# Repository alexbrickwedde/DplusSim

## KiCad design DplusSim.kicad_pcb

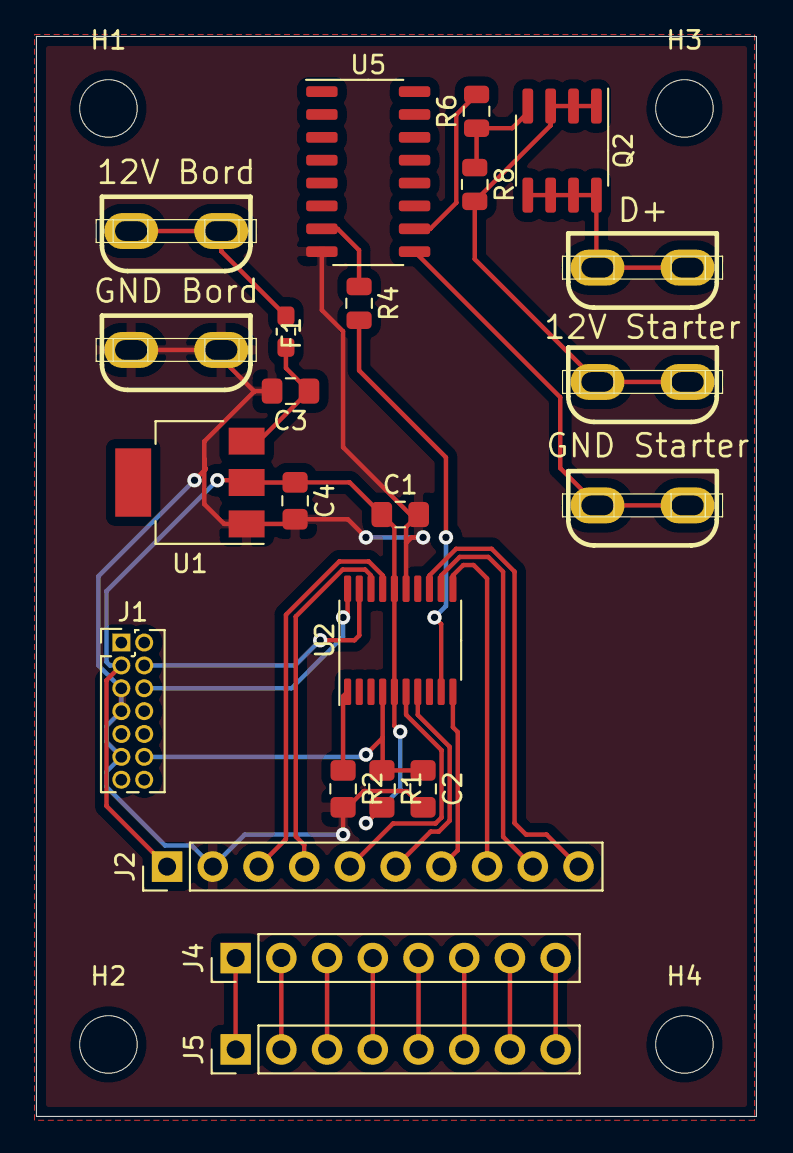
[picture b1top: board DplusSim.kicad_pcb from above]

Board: 2 copper layers, 40.0 x 60.0 mm, 27 parts (0 on the bottom side), 31 nets.

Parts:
C1: 100n; C_0805_2012Metric_Pad1.15x1.40mm_HandSolder
C2, C3, C4: C; C_0805_2012Metric_Pad1.15x1.40mm_HandSolder
F1: Polyfuse; R_0603_1608Metric_Pad1.05x0.95mm_HandSolder
H1, H2, H3, H4: MountingHole; MountingHole_3.2mm_M3_DIN965
J1: Conn_02x07_Odd_Even; PinHeader_2x07_P1.27mm_Vertical
J2: Conn_01x10; PinHeader_1x10_P2.54mm_Vertical
J3: GND Starter; FASTON-6_3mm
J4, J5: Conn_01x08; PinHeader_1x08_P2.54mm_Vertical
J6: 12V Starter; FASTON-6_3mm
J7: 12V Bord; FASTON-6_3mm
J8: GND Bord; FASTON-6_3mm
J11: D+; FASTON-6_3mm
Q2: IRF7404; SOIC-8_3.9x4.9mm_P1.27mm
R1, R2: R; R_0805_2012Metric_Pad1.15x1.40mm_HandSolder
R4, R6, R8: R; R_0805_2012Metric
U1: LT1117-3.3; SOT-223
U2: STM32L031F4Px; TSSOP-20_4.4x6.5mm_P0.65mm
U5: LTV-847; SO-16_3.9x9.9mm_P1.27mm

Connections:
+3V3: C1.1, C4.1, J1.3, J2.1, R1.2, U1.2, U2.5, U2.16
+12V: C3.1, F1.1, U1.3
+12VA: J6.1, Q2.1, Q2.2, Q2.3, R8.2
/Dplus: J11.1, Q2.5, Q2.6, Q2.7, Q2.8
/Dplus_out: R4.2, U2.9
/EN: J2.6, U2.7
/I2C_SCL: J2.3, U2.17
/I2C_SDA: J2.4, U2.18
/INT: J2.5, U2.6
/NRST: C2.1, J1.12, R1.1, U2.4
/SPI_MISO: J2.9, U2.12
/SPI_MOSI: J2.10, U2.13
/SPI_NSS: J2.7, U2.10
/SPI_SCK: J2.8, U2.11
/SWDCLK: J1.6, U2.20
/SWDIO: J1.4, U2.19
GND: C1.2, C2.2, C3.2, C4.2, J1.5, J1.7, J1.11, J2.2, J8.1, R2.2, U1.1, U2.15, U5.8
GNDA: J3.1, U5.9
unnamed: F1.2, J7.1
unnamed: J4.1, J5.1
unnamed: J4.2, J5.2
unnamed: J4.3, J5.3
unnamed: J4.4, J5.4
unnamed: J4.5, J5.5
unnamed: J4.6, J5.6
unnamed: J4.7, J5.7
unnamed: J4.8, J5.8
unnamed: Q2.4, R6.1, R8.1
unnamed: R2.1, U2.1
unnamed: R4.1, U5.7
unnamed: R6.2, U5.10

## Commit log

2021-03-25 First
